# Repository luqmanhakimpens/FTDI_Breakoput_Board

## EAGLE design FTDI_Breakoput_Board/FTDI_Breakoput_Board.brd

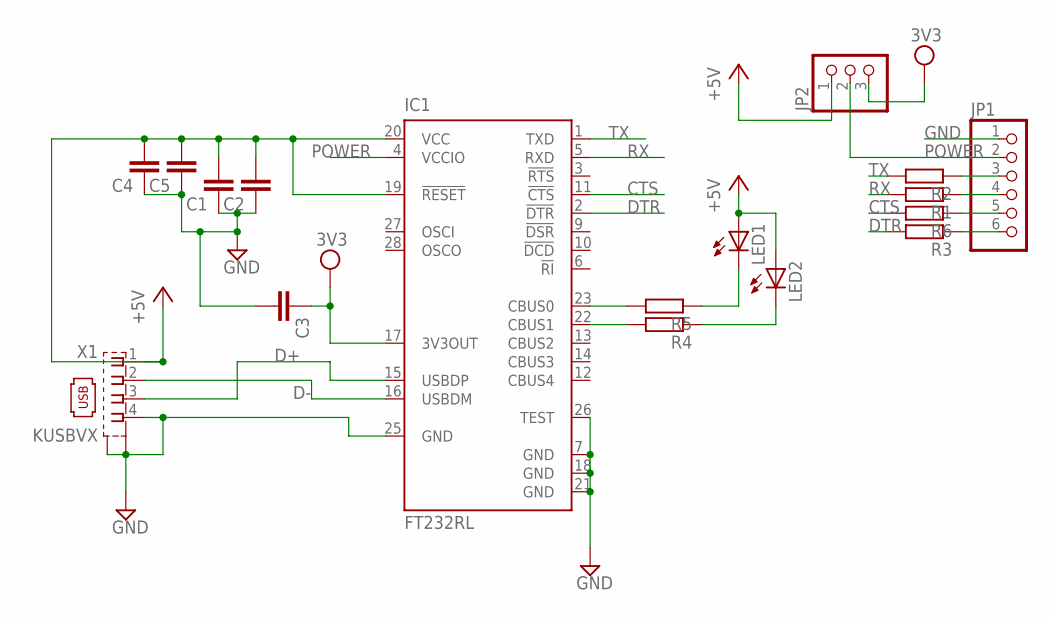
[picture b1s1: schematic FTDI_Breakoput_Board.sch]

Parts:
C1, C2, C3, C4, C5: C-EUC0805; C0805
IC1: FT232RL; SSOP28
JP1: PINHD-1X6; 1X06
JP2: PINHD-1X3; 1X03
LED1, LED2: LEDSML0805; SML0805
R1, R2, R3, R4, R5, R6: R-EU_R0805; R0805
X1: KUSBVX

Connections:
3V3: C3.1, IC1.17 (3V3OUT), JP2.3
CTS: IC1.11 (!CTS), R6.2
D+: IC1.15 (USBDP), X1.3
D-: IC1.16 (USBDM), X1.2
DTR: IC1.2 (!DTR), R3.2
GND: C1.1, C2.1, C3.2, C4.1, C5.1, IC1.7 (GND), IC1.18 (GND), IC1.21 (GND), IC1.25 (GND), IC1.26 (TEST), JP1.1, X1.4, X1.M1 (S1), X1.M2 (S2)
unnamed: JP1.3, R2.1
unnamed: JP1.4, R1.1
unnamed: JP1.5, R6.1
unnamed: IC1.23 (CBUS0), R5.2
unnamed: IC1.22 (CBUS1), R4.2
unnamed: JP1.6, R3.1
unnamed: LED1.C, R5.1
unnamed: LED2.C, R4.1
POWER: IC1.4 (VCCIO), JP1.2, JP2.2
RX: IC1.5 (RXD), R1.2
TX: IC1.1 (TXD), R2.2
VCC: C1.2, C2.2, C4.2, C5.2, IC1.19 (!RESET), IC1.20 (VCC), JP2.1, LED1.A, LED2.A, X1.1

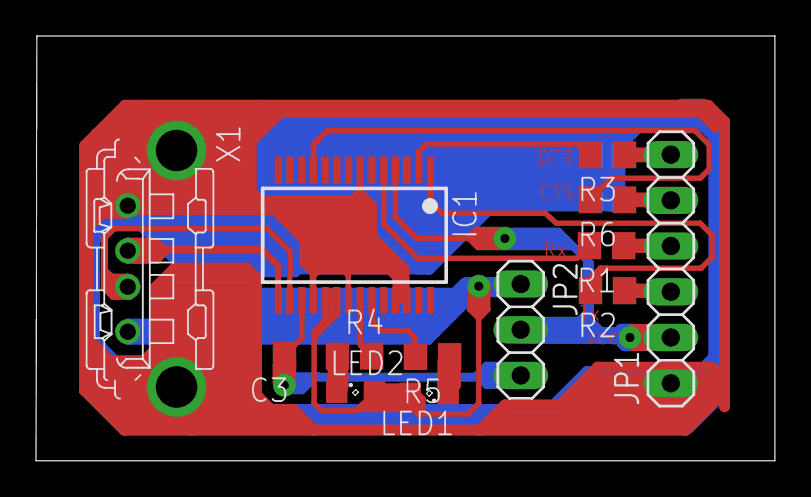
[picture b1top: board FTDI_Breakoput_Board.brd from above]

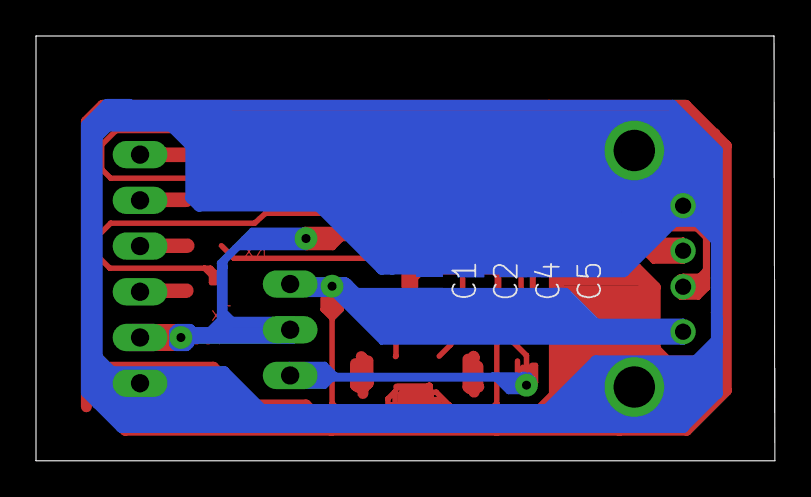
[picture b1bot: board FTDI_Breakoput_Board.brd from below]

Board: 2 copper layers, 41.0 x 23.6 mm, 17 parts (4 on the bottom side), 18 nets.

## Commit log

2018-07-26 first
2018-07-26 second
2018-07-26 third
